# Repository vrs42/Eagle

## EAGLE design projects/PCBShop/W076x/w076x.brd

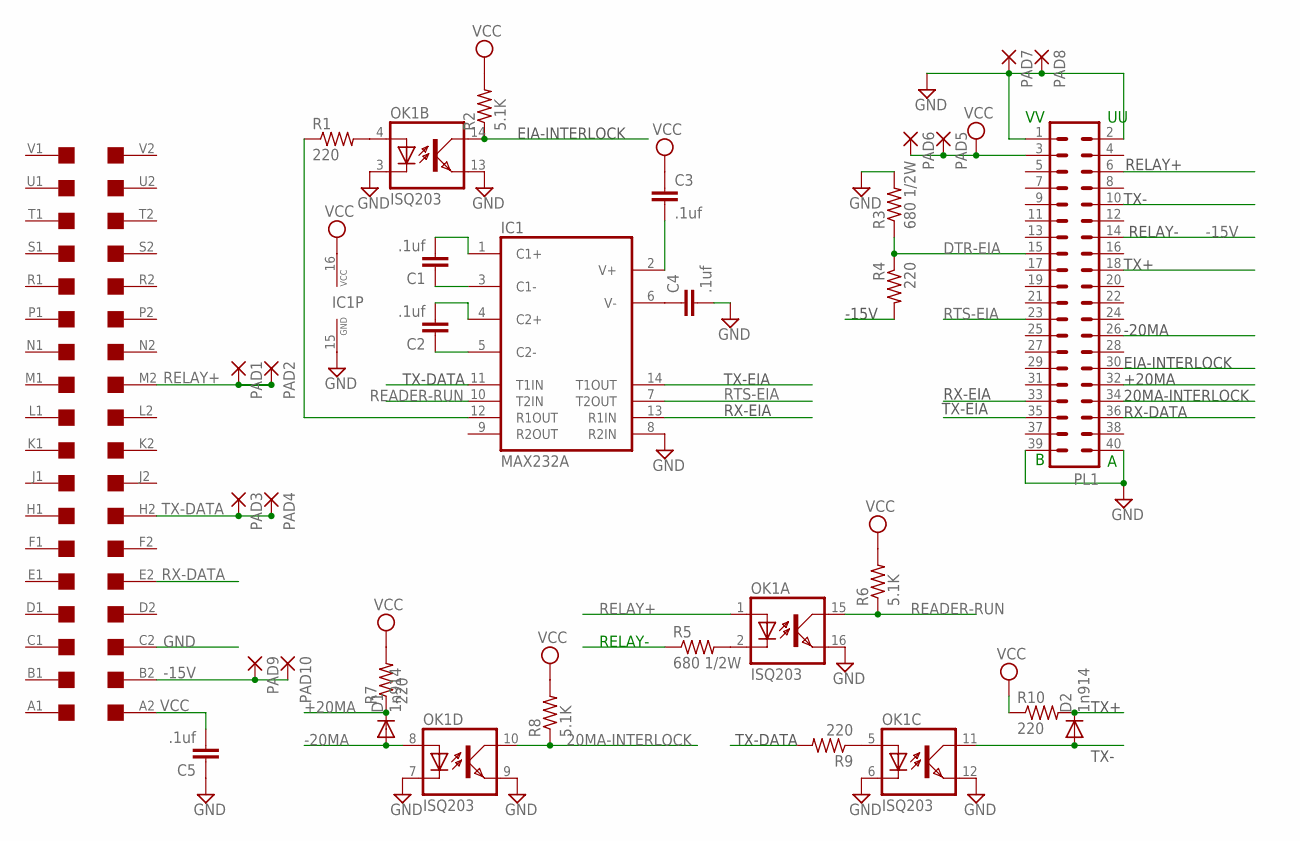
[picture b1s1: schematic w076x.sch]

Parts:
C1, C2, C3, C4, C5: .1uf; C050-025X075
D1, D2: 1n914; DO41-10
IC1: MAX232A; DIL16
OK1: ISQ203; DIL16
PAD1, PAD2, PAD3, PAD4, PAD5, PAD6, PAD7, PAD8, PAD9, PAD10: 1,6/0,8
PL1: 40H
R1, R4, R7, R9, R10: 220; 0207/10
R2, R6, R8: 5.1K; 0207/10
R3, R5: 680 1/2W; 0207/12
U$1: DEC-FLIPCHIP

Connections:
20MA-INTERLOCK: OK1.10 (COL), PL1.34, R8.1
+20MA: D1.C, PL1.32, R7.1
-15V: PAD9.1, PAD10.1, PL1.14, R4.2, R5.1, U$1.B2
-20MA: D1.A, OK1.8 (A), PL1.26
DTR-EIA: PL1.15, R3.1, R4.1
EIA-INTERLOCK: OK1.14 (COL), PL1.30, R2.1
GND: C4.2, C5.1, IC1.8 (R2IN), IC1.15 (GND), OK1.3 (C), OK1.6 (C), OK1.7 (C), OK1.9 (EMIT), OK1.12 (EMIT), OK1.13 (EMIT), OK1.16 (EMIT), PAD7.1, PAD8.1, PL1.1, PL1.2, PL1.39, PL1.40, R3.2, U$1.C2
unnamed: C2.1, IC1.5 (C2-)
unnamed: C2.2, IC1.4 (C2+)
unnamed: C1.2, IC1.1 (C1+)
unnamed: C1.1, IC1.3 (C1-)
unnamed: OK1.2 (C), R5.2
unnamed: IC1.12 (R1OUT), R1.1
unnamed: C3.2, IC1.2 (V+)
unnamed: C4.1, IC1.6 (V-)
unnamed: OK1.4 (A), R1.2
unnamed: OK1.5 (A), R9.1
READER-RUN: IC1.10 (T2IN), OK1.15 (COL), R6.1
RELAY+: OK1.1 (A), PAD1.1, PAD2.1, PL1.6, U$1.M2
RTS-EIA: IC1.7 (T2OUT), PL1.23
RX-DATA: PL1.36, U$1.E2
RX-EIA: IC1.13 (R1IN), PL1.33
TX+: D2.C, PL1.18, R10.2
TX-: D2.A, OK1.11 (COL), PL1.10
TX-DATA: IC1.11 (T1IN), PAD3.1, PAD4.1, R9.2, U$1.H2
TX-EIA: IC1.14 (T1OUT), PL1.35
VCC: C3.1, C5.2, IC1.16 (VCC), PAD5.1, PAD6.1, PL1.3, R2.2, R6.2, R7.2, R8.2, R10.1, U$1.A2

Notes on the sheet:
TX-
TX+
RX-EIA
TX-EIA
-20MA
EIA-INTERLOCK
+20MA
20MA-INTERLOCK
RX-DATA
RELAY+
RELAY-
TX-DATA
-15V

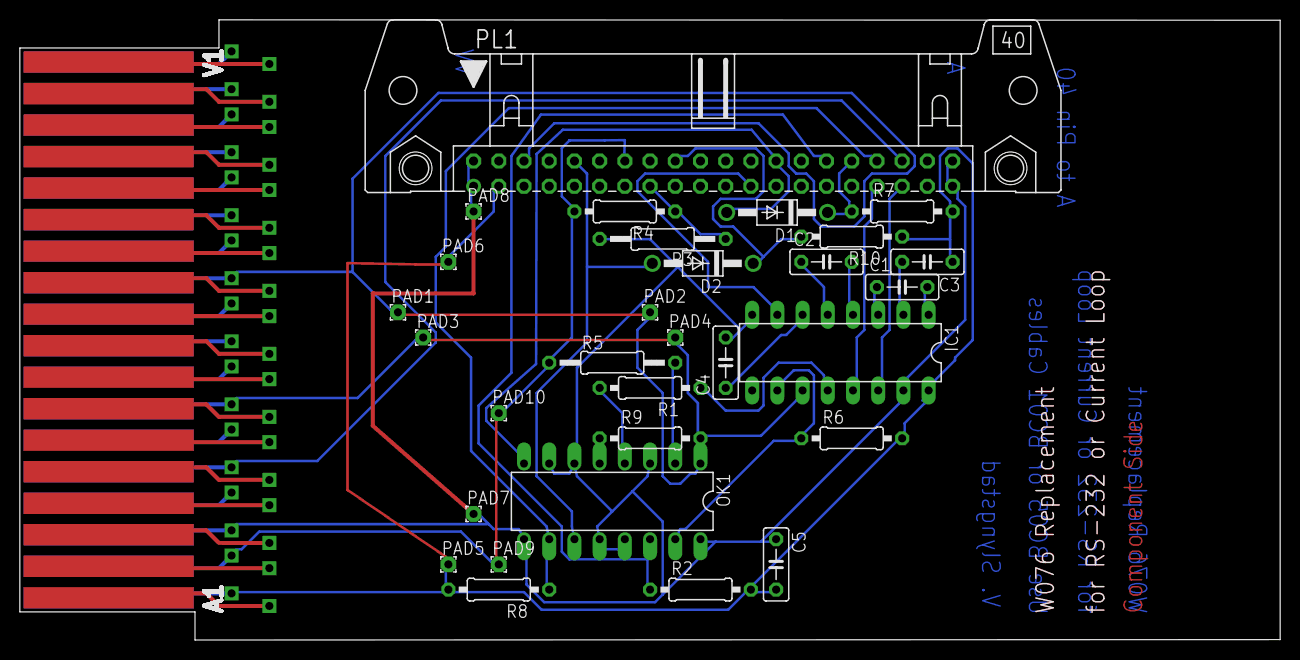
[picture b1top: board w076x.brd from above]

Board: 2 copper layers, 127.0 x 62.5 mm, 31 parts (0 on the bottom side), 27 nets.

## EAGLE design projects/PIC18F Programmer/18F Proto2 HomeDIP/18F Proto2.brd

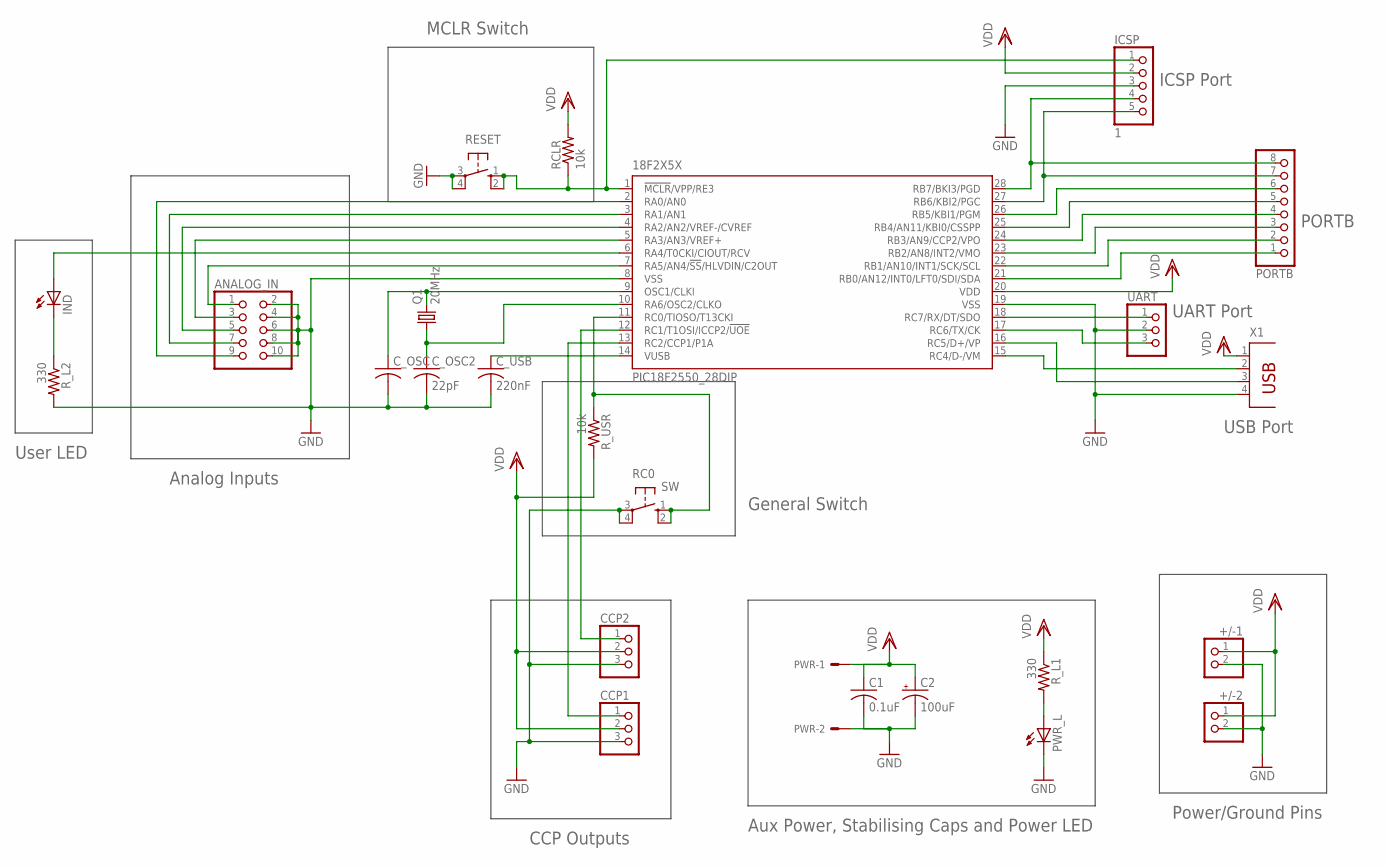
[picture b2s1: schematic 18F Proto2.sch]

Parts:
18F2X5X: PIC18F2550_28DIP; DIL28-3
+/-1, +/-2: PINHD-1X2; 1X02
ANALOG_IN: PINHD-2X5; 2X05
C1: 0.1uF; C050-025X075
C2: 100uF; E2,5-6
CCP1, CCP2: PINHD-1X3; 1X03
C_OSC: C-US025-025X050; C025-025X050
C_OSC2: 22pF; C025-025X050
C_USB: 220nF; C050-025X075
ICSP: 1; 1X05
IND: LED3MM
PORTB: PINHD-1X8; 1X08
PWR: 22-23-2021
PWR_L: LED3MM
Q1: 20MHz; HC49/S
RC0: SW; B3F-10XX
RCLR: 10k; 0204/7
RESET: 10-XX; B3F-10XX
R_L1: 330; 0204/7
R_L2: 330; 0207/10
R_USR: 10k; 0204/7
UART: PINHD-1X3; 1X03
X1: PN61729

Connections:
D+: 18F2X5X.16 (RC5/D+/VP), X1.3
D-: 18F2X5X.15 (RC4/D-/VM), X1.2
GND: 18F2X5X.8 (VSS), 18F2X5X.19 (VSS), +/-1.2, +/-2.2, ANALOG_IN.2, ANALOG_IN.4, ANALOG_IN.6, ANALOG_IN.8, ANALOG_IN.10, C1.2, C2.-, CCP1.3, CCP2.3, C_OSC.2, C_OSC2.2, C_USB.2, ICSP.3, PWR.2, PWR_L.K (C), RC0.3, RC0.4 (P1), RESET.3, RESET.4 (P1), R_L2.2, UART.2, X1.4
MCLR: 18F2X5X.1 (!MCLR!/VPP/RE3), ICSP.1, RCLR.1, RESET.1 (S), RESET.2 (S1)
unnamed: 18F2X5X.10 (RA6/OSC2/CLKO), C_OSC2.1, Q1.1
unnamed: PWR_L.A, R_L1.2
unnamed: 18F2X5X.9 (OSC1/CLKI), C_OSC.1, Q1.2
unnamed: 18F2X5X.14 (VUSB), C_USB.1
unnamed: 18F2X5X.2 (RA0/AN0), ANALOG_IN.9
unnamed: 18F2X5X.3 (RA1/AN1), ANALOG_IN.7
unnamed: 18F2X5X.4 (RA2/AN2/VREF-/CVREF), ANALOG_IN.5
unnamed: 18F2X5X.5 (RA3/AN3/VREF+), ANALOG_IN.3
unnamed: 18F2X5X.6 (RA4/T0CKI/CIOUT/RCV), IND.A
unnamed: 18F2X5X.7 (RA5/AN4/!SS!/HLVDIN/C2OUT), ANALOG_IN.1
unnamed: IND.K (C), R_L2.1
unnamed: 18F2X5X.11 (RC0/TIOSO/T13CKI), RC0.1 (S), RC0.2 (S1), R_USR.1
unnamed: 18F2X5X.12 (RC1/T1OSI/ICCP2/!UOE), CCP2.1
unnamed: 18F2X5X.13 (RC2/CCP1/P1A), CCP1.1
unnamed: 18F2X5X.21 (RB0/AN12/INT0/LFT0/SDI/SDA), PORTB.1
unnamed: 18F2X5X.22 (RB1/AN10/INT1/SCK/SCL), PORTB.2
unnamed: 18F2X5X.23 (RB2/AN8/INT2/VMO), PORTB.3
unnamed: 18F2X5X.24 (RB3/AN9/CCP2/VPO), PORTB.4
unnamed: 18F2X5X.25 (RB4/AN11/KBI0/CSSPP), PORTB.5
unnamed: 18F2X5X.26 (RB5/KBI1/PGM), PORTB.6
PGC: 18F2X5X.27 (RB6/KBI2/PGC), ICSP.5, PORTB.7
PGD: 18F2X5X.28 (RB7/BKI3/PGD), ICSP.4, PORTB.8
RX: 18F2X5X.18 (RC7/RX/DT/SDO), UART.1
TX: 18F2X5X.17 (RC6/TX/CK), UART.3
VDD: 18F2X5X.20 (VDD), +/-1.1, +/-2.1, C1.1, C2.+, CCP1.2, CCP2.2, ICSP.2, PWR.1, RCLR.2, R_L1.1, R_USR.2, X1.1

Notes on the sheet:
Power/Ground Pins
Aux Power, Stabilising Caps and Power LED
General Switch
User LED
Analog Inputs
CCP Outputs
MCLR Switch
ICSP Port
PORTB
UART Port
USB Port

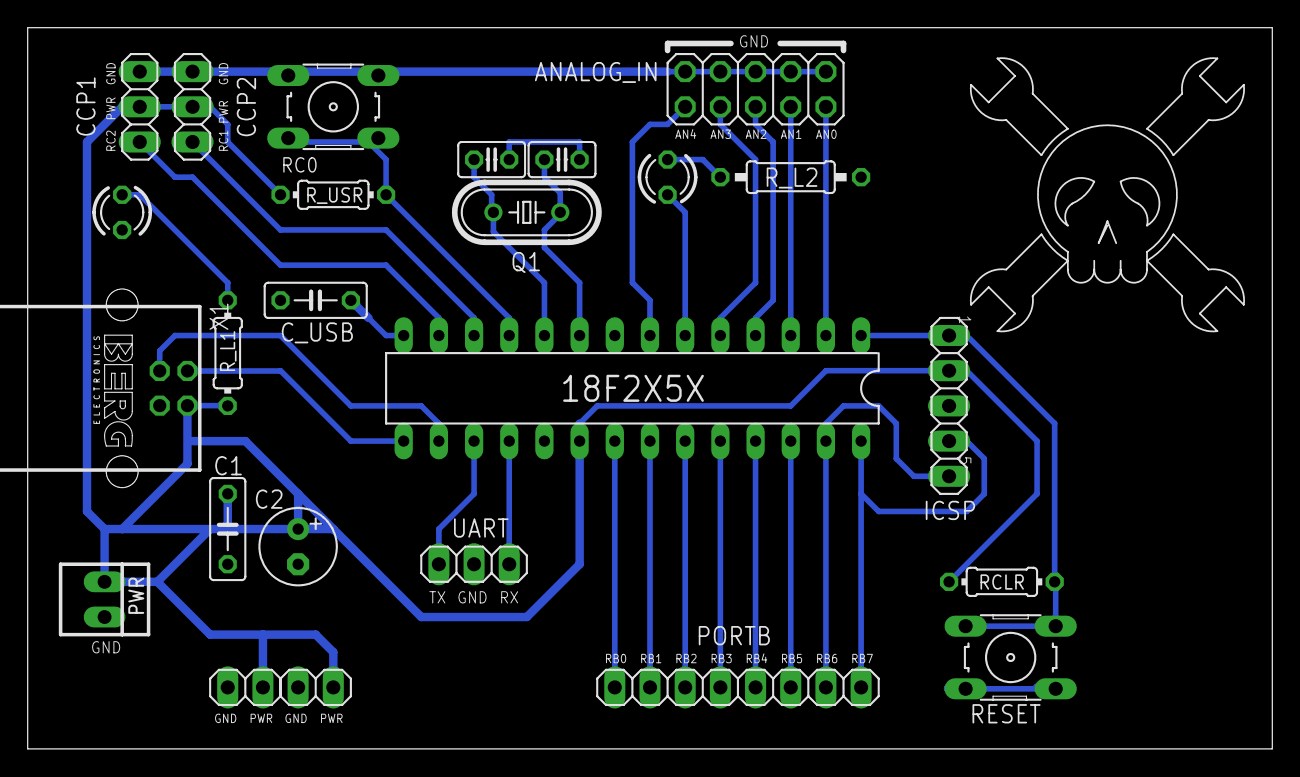
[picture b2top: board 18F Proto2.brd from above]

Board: 2 copper layers, 89.8 x 52.1 mm, 26 parts (0 on the bottom side), 29 nets.

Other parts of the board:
U$1: HACKADAY_S

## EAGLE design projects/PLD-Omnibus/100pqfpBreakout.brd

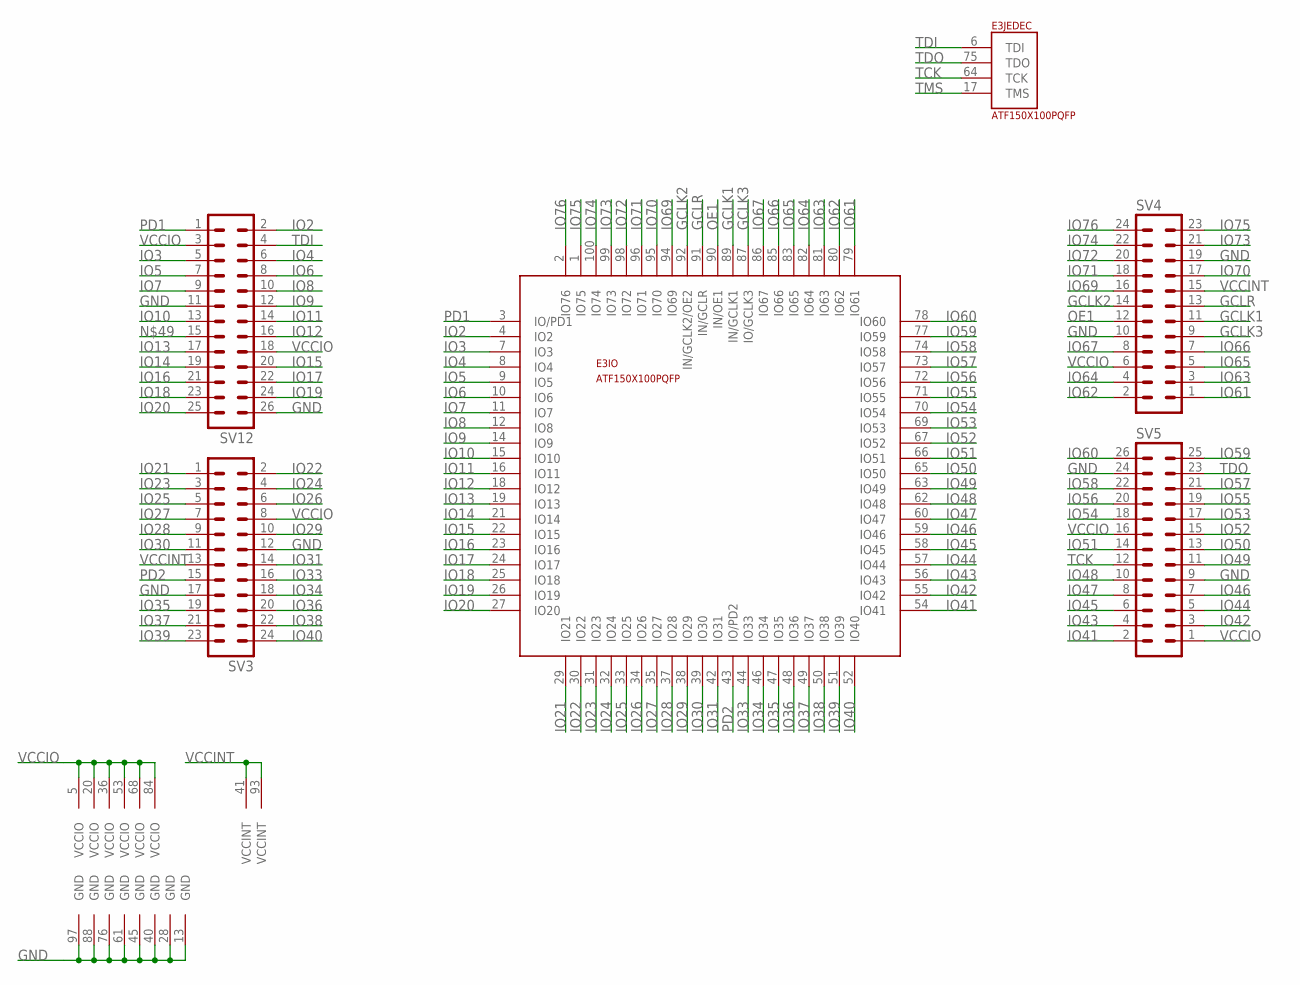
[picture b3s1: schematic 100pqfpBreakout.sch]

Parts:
E3: ATF150X100PQFP; PQFP-100
SV3, SV4: MA12-2
SV5, SV12: MA13-2

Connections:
GCLK1: E3.89 (IN/GCLK1), SV4.11
GCLK2: E3.92 (IN/GCLK2/OE2), SV4.14
GCLK3: E3.87 (IO/GCLK3), SV4.9
GCLR: E3.91 (IN/GCLR), SV4.13
GND: E3.13 (GND), E3.28 (GND), E3.40 (GND), E3.45 (GND), E3.61 (GND), E3.76 (GND), E3.88 (GND), E3.97 (GND), SV3.12, SV3.17, SV4.10, SV4.19, SV5.9, SV5.24, SV12.11, SV12.26
IO2: E3.4 (IO2), SV12.2
IO3: E3.7 (IO3), SV12.5
IO4: E3.8 (IO4), SV12.6
IO5: E3.9 (IO5), SV12.7
IO6: E3.10 (IO6), SV12.8
IO7: E3.11 (IO7), SV12.9
IO8: E3.12 (IO8), SV12.10
IO9: E3.14 (IO9), SV12.12
IO10: E3.15 (IO10), SV12.13
IO11: E3.16 (IO11), SV12.14
IO12: E3.18 (IO12), SV12.16
IO13: E3.19 (IO13), SV12.17
IO14: E3.21 (IO14), SV12.19
IO15: E3.22 (IO15), SV12.20
IO16: E3.23 (IO16), SV12.21
IO17: E3.24 (IO17), SV12.22
IO18: E3.25 (IO18), SV12.23
IO19: E3.26 (IO19), SV12.24
IO20: E3.27 (IO20), SV12.25
IO21: E3.29 (IO21), SV3.1
IO22: E3.30 (IO22), SV3.2
IO23: E3.31 (IO23), SV3.3
IO24: E3.32 (IO24), SV3.4
IO25: E3.33 (IO25), SV3.5
IO26: E3.34 (IO26), SV3.6
IO27: E3.35 (IO27), SV3.7
IO28: E3.37 (IO28), SV3.9
IO29: E3.38 (IO29), SV3.10
IO30: E3.39 (IO30), SV3.11
IO31: E3.42 (IO31), SV3.14
IO33: E3.44 (IO33), SV3.16
IO34: E3.46 (IO34), SV3.18
IO35: E3.47 (IO35), SV3.19
IO36: E3.48 (IO36), SV3.20
IO37: E3.49 (IO37), SV3.21
IO38: E3.50 (IO38), SV3.22
IO39: E3.51 (IO39), SV3.23
IO40: E3.52 (IO40), SV3.24
IO41: E3.54 (IO41), SV5.2
IO42: E3.55 (IO42), SV5.3
IO43: E3.56 (IO43), SV5.4
IO44: E3.57 (IO44), SV5.5
IO45: E3.58 (IO45), SV5.6
IO46: E3.59 (IO46), SV5.7
IO47: E3.60 (IO47), SV5.8
IO48: E3.62 (IO48), SV5.10
IO49: E3.63 (IO49), SV5.11
IO50: E3.65 (IO50), SV5.13
IO51: E3.66 (IO51), SV5.14
IO52: E3.67 (IO52), SV5.15
IO53: E3.69 (IO53), SV5.17
IO54: E3.70 (IO54), SV5.18
IO55: E3.71 (IO55), SV5.19
IO56: E3.72 (IO56), SV5.20
IO57: E3.73 (IO57), SV5.21
IO58: E3.74 (IO58), SV5.22
IO59: E3.77 (IO59), SV5.25
IO60: E3.78 (IO60), SV5.26
IO61: E3.79 (IO61), SV4.1
IO62: E3.80 (IO62), SV4.2
IO63: E3.81 (IO63), SV4.3
IO64: E3.82 (IO64), SV4.4
IO65: E3.83 (IO65), SV4.5
IO66: E3.85 (IO66), SV4.7
IO67: E3.86 (IO67), SV4.8
IO69: E3.94 (IO69), SV4.16
IO70: E3.95 (IO70), SV4.17
IO71: E3.96 (IO71), SV4.18
IO72: E3.98 (IO72), SV4.20
IO73: E3.99 (IO73), SV4.21
IO74: E3.100 (IO74), SV4.22
IO75: E3.1 (IO75), SV4.23
IO76: E3.2 (IO76), SV4.24
OE1: E3.90 (IN/OE1), SV4.12
PD1: E3.3 (IO/PD1), SV12.1
PD2: E3.43 (IO/PD2), SV3.15
TCK: E3.64 (TCK), SV5.12
TDI: E3.6 (TDI), SV12.4
TDO: E3.75 (TDO), SV5.23
TMS: E3.17 (TMS)
VCCINT: E3.41 (VCCINT), E3.93 (VCCINT), SV3.13, SV4.15
VCCIO: E3.5 (VCCIO), E3.20 (VCCIO), E3.36 (VCCIO), E3.53 (VCCIO), E3.68 (VCCIO), E3.84 (VCCIO), SV3.8, SV4.6, SV5.1, SV5.16, SV12.3, SV12.18

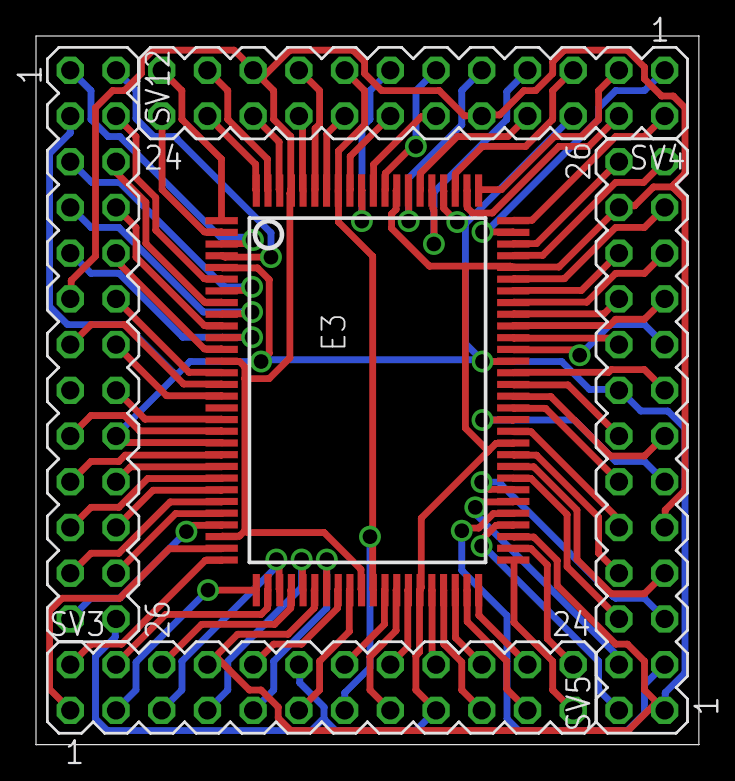
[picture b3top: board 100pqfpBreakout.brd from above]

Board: 2 copper layers, 36.8 x 39.4 mm, 5 parts (0 on the bottom side), 86 nets.

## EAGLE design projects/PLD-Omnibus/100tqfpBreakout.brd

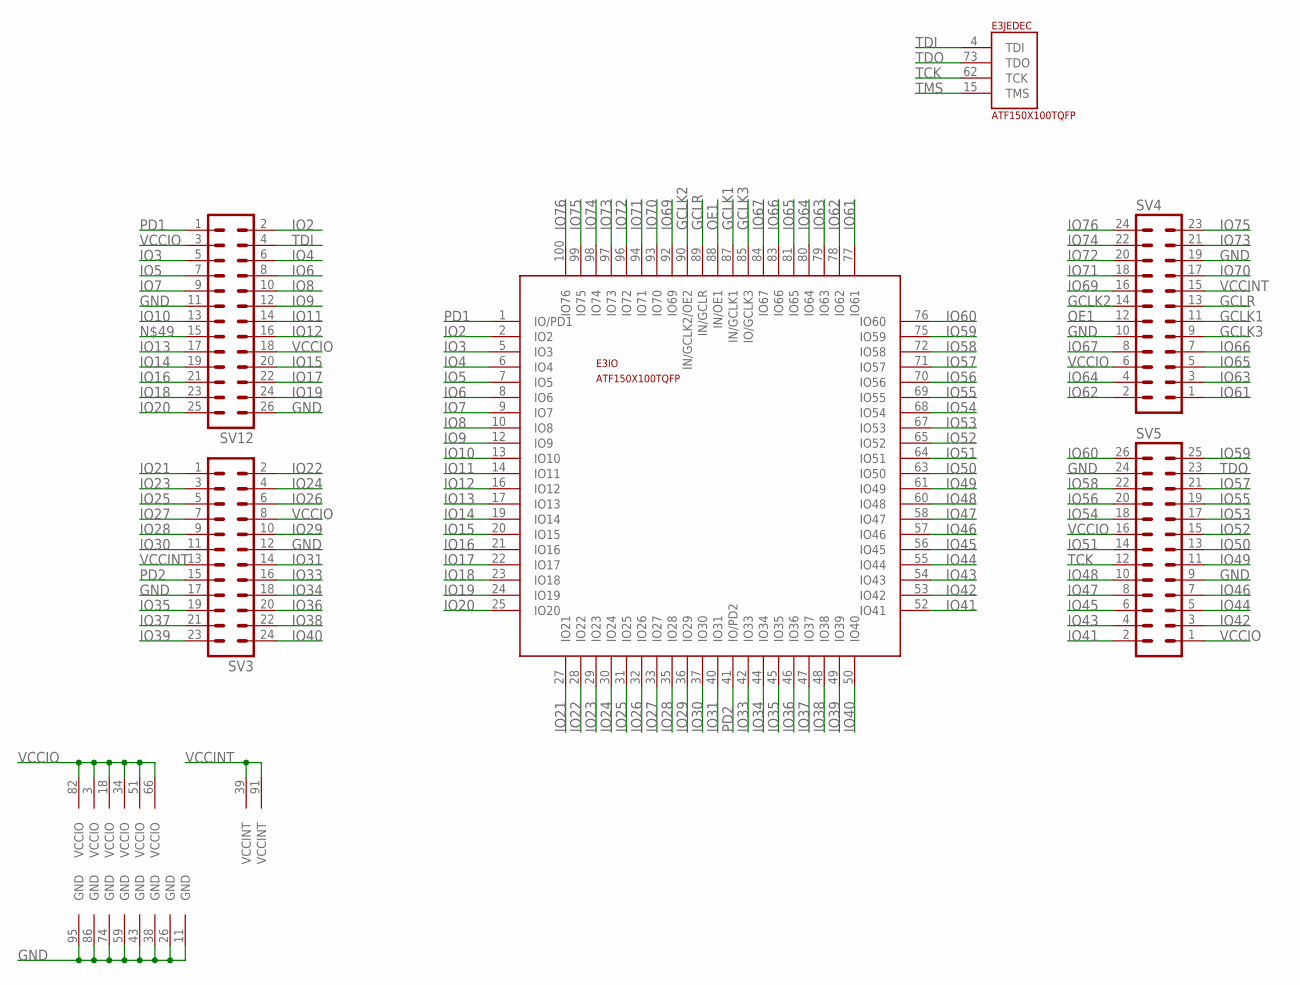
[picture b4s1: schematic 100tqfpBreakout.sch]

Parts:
E3: ATF150X100TQFP; TQFP-100
SV3, SV4: MA12-2
SV5, SV12: MA13-2

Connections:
GCLK1: E3.87 (IN/GCLK1), SV4.11
GCLK2: E3.90 (IN/GCLK2/OE2), SV4.14
GCLK3: E3.85 (IO/GCLK3), SV4.9
GCLR: E3.89 (IN/GCLR), SV4.13
GND: E3.11 (GND), E3.26 (GND), E3.38 (GND), E3.43 (GND), E3.59 (GND), E3.74 (GND), E3.86 (GND), E3.95 (GND), SV3.12, SV3.17, SV4.10, SV4.19, SV5.9, SV5.24, SV12.11, SV12.26
IO2: E3.2 (IO2), SV12.2
IO3: E3.5 (IO3), SV12.5
IO4: E3.6 (IO4), SV12.6
IO5: E3.7 (IO5), SV12.7
IO6: E3.8 (IO6), SV12.8
IO7: E3.9 (IO7), SV12.9
IO8: E3.10 (IO8), SV12.10
IO9: E3.12 (IO9), SV12.12
IO10: E3.13 (IO10), SV12.13
IO11: E3.14 (IO11), SV12.14
IO12: E3.16 (IO12), SV12.16
IO13: E3.17 (IO13), SV12.17
IO14: E3.19 (IO14), SV12.19
IO15: E3.20 (IO15), SV12.20
IO16: E3.21 (IO16), SV12.21
IO17: E3.22 (IO17), SV12.22
IO18: E3.23 (IO18), SV12.23
IO19: E3.24 (IO19), SV12.24
IO20: E3.25 (IO20), SV12.25
IO21: E3.27 (IO21), SV3.1
IO22: E3.28 (IO22), SV3.2
IO23: E3.29 (IO23), SV3.3
IO24: E3.30 (IO24), SV3.4
IO25: E3.31 (IO25), SV3.5
IO26: E3.32 (IO26), SV3.6
IO27: E3.33 (IO27), SV3.7
IO28: E3.35 (IO28), SV3.9
IO29: E3.36 (IO29), SV3.10
IO30: E3.37 (IO30), SV3.11
IO31: E3.40 (IO31), SV3.14
IO33: E3.42 (IO33), SV3.16
IO34: E3.44 (IO34), SV3.18
IO35: E3.45 (IO35), SV3.19
IO36: E3.46 (IO36), SV3.20
IO37: E3.47 (IO37), SV3.21
IO38: E3.48 (IO38), SV3.22
IO39: E3.49 (IO39), SV3.23
IO40: E3.50 (IO40), SV3.24
IO41: E3.52 (IO41), SV5.2
IO42: E3.53 (IO42), SV5.3
IO43: E3.54 (IO43), SV5.4
IO44: E3.55 (IO44), SV5.5
IO45: E3.56 (IO45), SV5.6
IO46: E3.57 (IO46), SV5.7
IO47: E3.58 (IO47), SV5.8
IO48: E3.60 (IO48), SV5.10
IO49: E3.61 (IO49), SV5.11
IO50: E3.63 (IO50), SV5.13
IO51: E3.64 (IO51), SV5.14
IO52: E3.65 (IO52), SV5.15
IO53: E3.67 (IO53), SV5.17
IO54: E3.68 (IO54), SV5.18
IO55: E3.69 (IO55), SV5.19
IO56: E3.70 (IO56), SV5.20
IO57: E3.71 (IO57), SV5.21
IO58: E3.72 (IO58), SV5.22
IO59: E3.75 (IO59), SV5.25
IO60: E3.76 (IO60), SV5.26
IO61: E3.77 (IO61), SV4.1
IO62: E3.78 (IO62), SV4.2
IO63: E3.79 (IO63), SV4.3
IO64: E3.80 (IO64), SV4.4
IO65: E3.81 (IO65), SV4.5
IO66: E3.83 (IO66), SV4.7
IO67: E3.84 (IO67), SV4.8
IO69: E3.92 (IO69), SV4.16
IO70: E3.93 (IO70), SV4.17
IO71: E3.94 (IO71), SV4.18
IO72: E3.96 (IO72), SV4.20
IO73: E3.97 (IO73), SV4.21
IO74: E3.98 (IO74), SV4.22
IO75: E3.99 (IO75), SV4.23
IO76: E3.100 (IO76), SV4.24
OE1: E3.88 (IN/OE1), SV4.12
PD1: E3.1 (IO/PD1), SV12.1
PD2: E3.41 (IO/PD2), SV3.15
TCK: E3.62 (TCK), SV5.12
TDI: E3.4 (TDI), SV12.4
TDO: E3.73 (TDO), SV5.23
TMS: E3.15 (TMS)
VCCINT: E3.39 (VCCINT), E3.91 (VCCINT), SV3.13, SV4.15
VCCIO: E3.3 (VCCIO), E3.18 (VCCIO), E3.34 (VCCIO), E3.51 (VCCIO), E3.66 (VCCIO), E3.82 (VCCIO), SV3.8, SV4.6, SV5.1, SV5.16, SV12.3, SV12.18

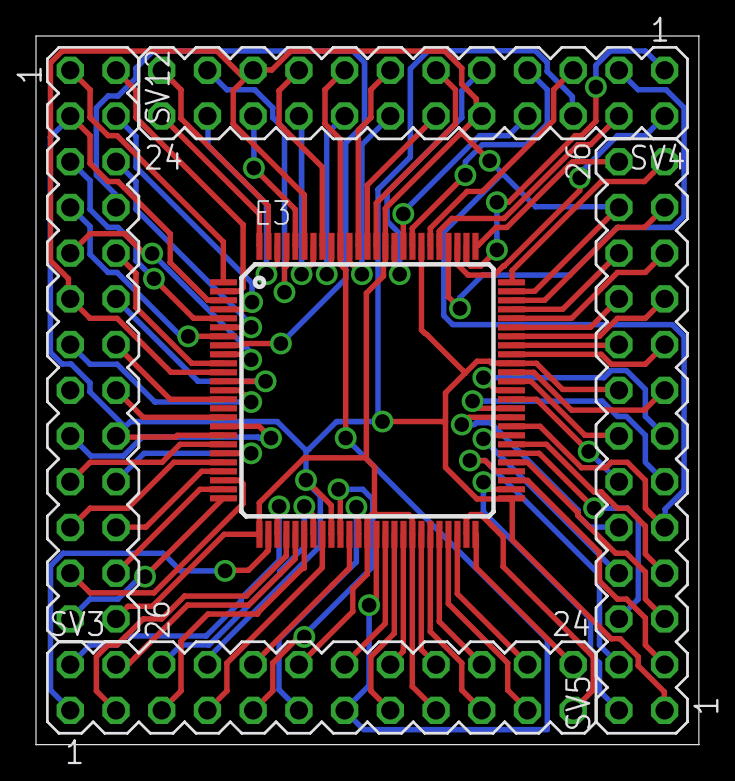
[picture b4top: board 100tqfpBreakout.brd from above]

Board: 2 copper layers, 36.8 x 39.4 mm, 5 parts (0 on the bottom side), 86 nets.

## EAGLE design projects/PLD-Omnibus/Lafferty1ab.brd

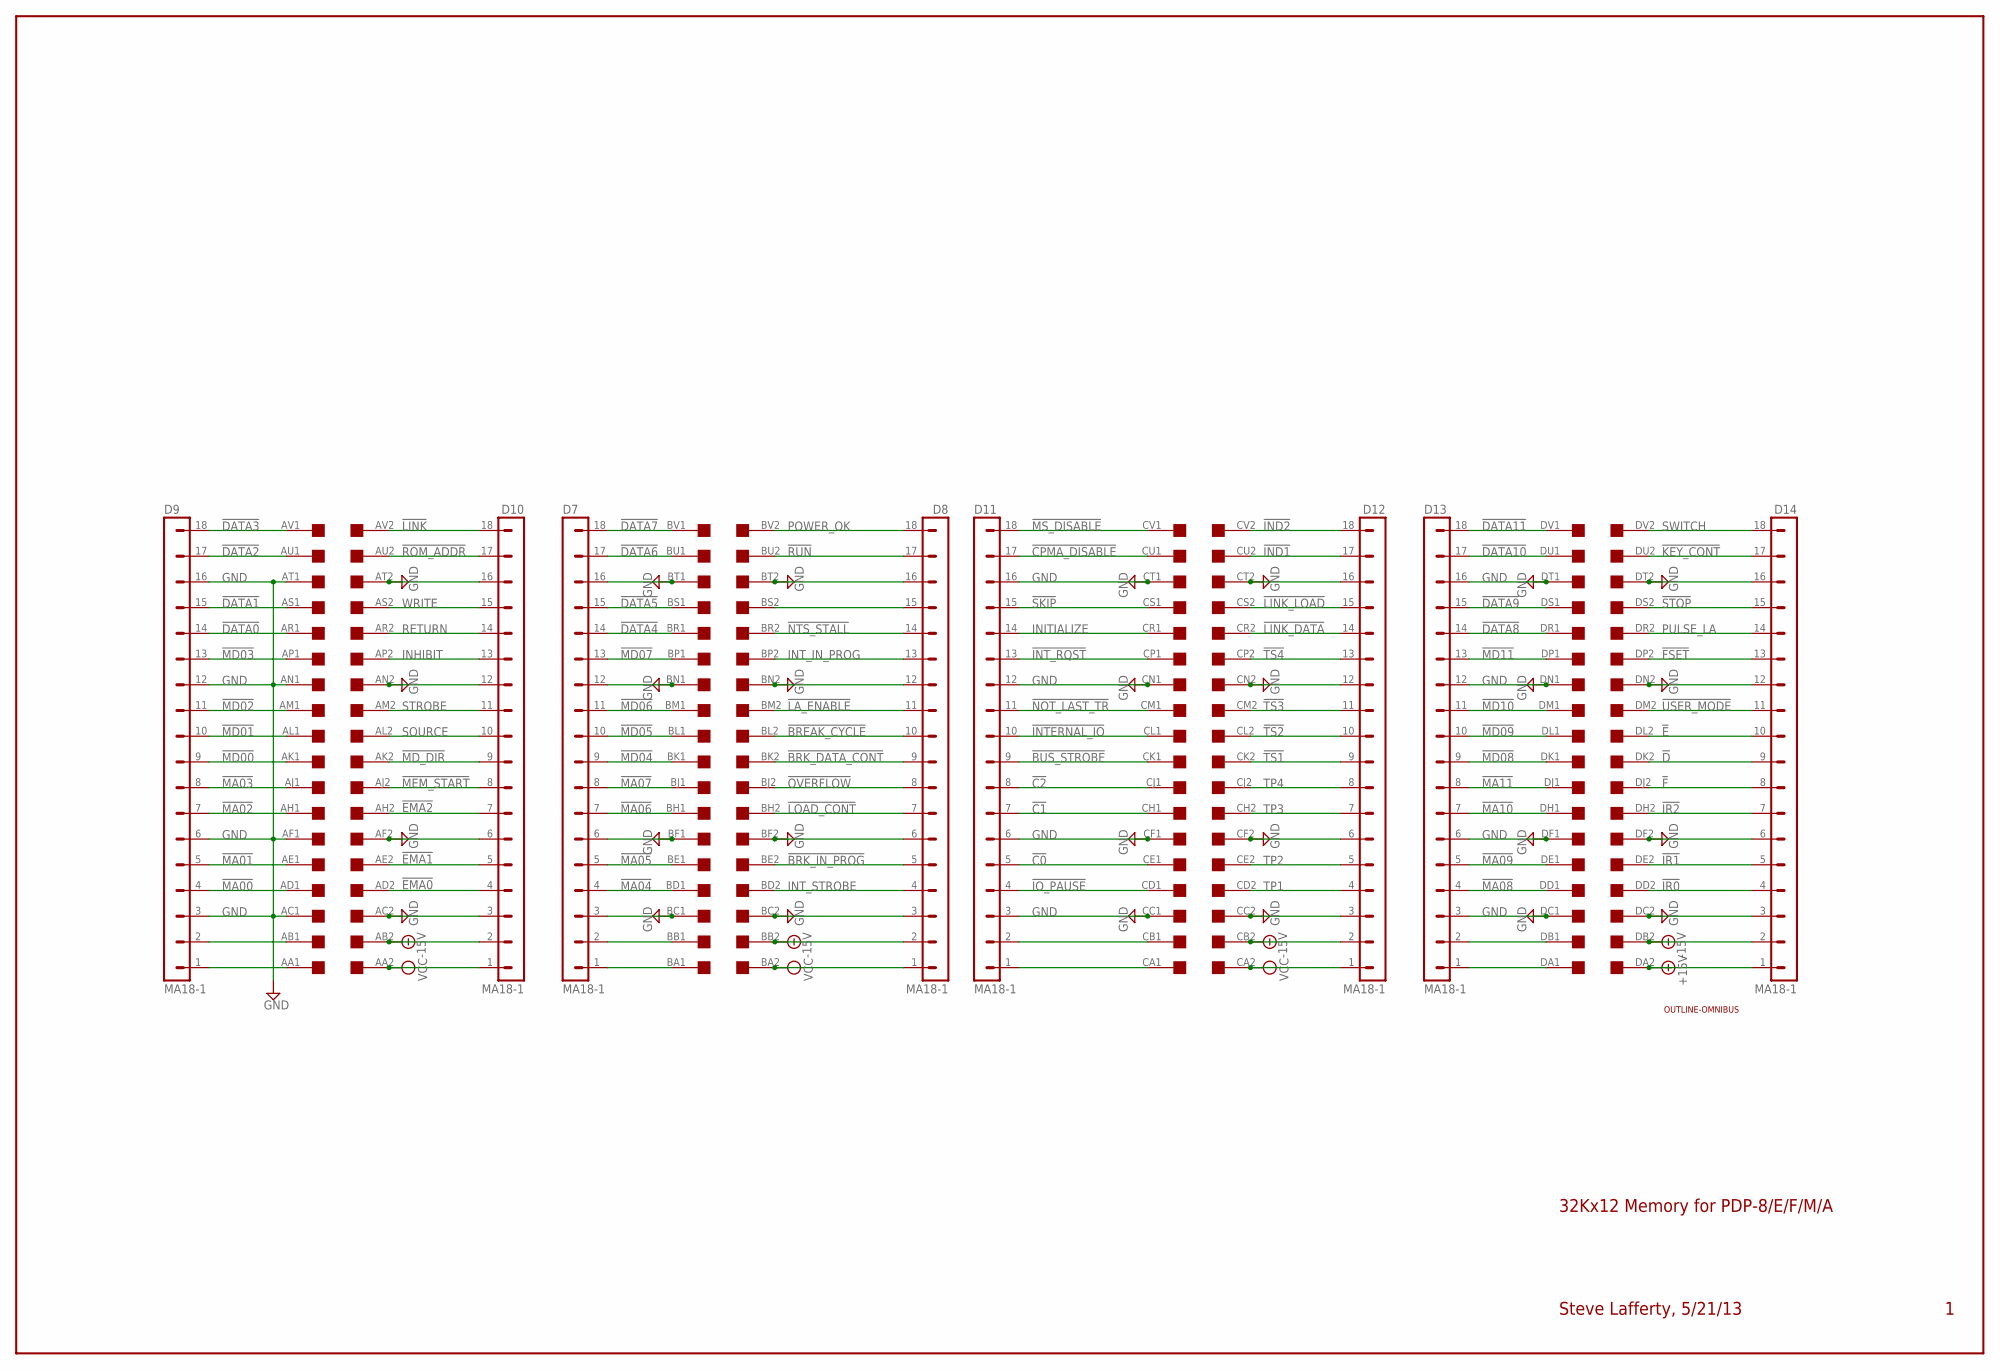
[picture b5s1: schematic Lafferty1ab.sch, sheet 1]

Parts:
D7, D8, D9, D10, D11, D12, D13, D14: MA18-1
U$1: OUTLINE-OMNIBUS; OMNIBUS
U$2: QUAD; EDGE-CON8

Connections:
!BREAK_CYCLE: D8.10, U$2.BL2
!BRK_DATA_CONT: D8.9, U$2.BK2
!BRK_IN_PROG: D8.5, U$2.BE2
!BUS_STROBE: D11.9, U$2.CK1
!C0: D11.5, U$2.CE1
!C1: D11.7, U$2.CH1
!C2: D11.8, U$2.CJ1
!CPMA_DISABLE: D11.17, U$2.CU1
!D: D14.9, U$2.DK2
!DATA0: D9.14, U$2.AR1
!DATA1: D9.15, U$2.AS1
!DATA2: D9.17, U$2.AU1
!DATA3: D9.18, U$2.AV1
!DATA4: D7.14, U$2.BR1
!DATA5: D7.15, U$2.BS1
!DATA6: D7.17, U$2.BU1
!DATA7: D7.18, U$2.BV1
!DATA8: D13.14, U$2.DR1
!DATA9: D13.15, U$2.DS1
!DATA10: D13.17, U$2.DU1
!DATA11: D13.18, U$2.DV1
!E: D14.10, U$2.DL2
!EMA0: D10.4, U$2.AD2; also elsewhere on the board
!EMA1: D10.5, U$2.AE2; also elsewhere on the board
!EMA2: D10.7, U$2.AH2; also elsewhere on the board
!F: D14.8, U$2.DJ2
!FSET: D14.13, U$2.DP2
!IND1: D12.17, U$2.CU2
!IND2: D12.18, U$2.CV2
!INTERNAL_IO: D11.10, U$2.CL1
!INT_RQST: D11.13, U$2.CP1
!IO_PAUSE: D11.4, U$2.CD1
!IR0: D14.4, U$2.DD2
!IR1: D14.5, U$2.DE2
!IR2: D14.7, U$2.DH2
!KEY_CONT: D14.17, U$2.DU2
!LA_ENABLE: D8.11, U$2.BM2
!LINK: D10.18, U$2.AV2
!LINK_DATA: D12.14, U$2.CR2
!LINK_LOAD: D12.15, U$2.CS2
!LOAD_CONT: D8.7, U$2.BH2
!MA00: D9.4, U$2.AD1; also elsewhere on the board
!MA01: D9.5, U$2.AE1; also elsewhere on the board
!MA02: D9.7, U$2.AH1; also elsewhere on the board
!MA03: D9.8, U$2.AJ1; also elsewhere on the board
!MA04: D7.4, U$2.BD1; also elsewhere on the board
!MA05: D7.5, U$2.BE1; also elsewhere on the board
!MA06: D7.7, U$2.BH1; also elsewhere on the board
!MA07: D7.8, U$2.BJ1; also elsewhere on the board
!MA08: D13.4, U$2.DD1; also elsewhere on the board
!MA09: D13.5, U$2.DE1; also elsewhere on the board
!MA10: D13.7, U$2.DH1; also elsewhere on the board
!MA11: D13.8, U$2.DJ1; also elsewhere on the board
!MD00: D9.9, U$2.AK1; also elsewhere on the board
!MD01: D9.10, U$2.AL1; also elsewhere on the board
!MD02: D9.11, U$2.AM1; also elsewhere on the board
!MD03: D9.13, U$2.AP1; also elsewhere on the board
!MD04: D7.9, U$2.BK1; also elsewhere on the board
!MD05: D7.10, U$2.BL1; also elsewhere on the board
!MD06: D7.11, U$2.BM1; also elsewhere on the board
!MD07: D7.13, U$2.BP1; also elsewhere on the board
!MD08: D13.9, U$2.DK1; also elsewhere on the board
!MD09: D13.10, U$2.DL1; also elsewhere on the board
!MD10: D13.11, U$2.DM1; also elsewhere on the board
!MD11: D13.13, U$2.DP1; also elsewhere on the board
!MD_DIR: D10.9, U$2.AK2; also elsewhere on the board
!MEM_START: D10.8, U$2.AJ2
!MS_DISABLE: D11.18, U$2.CV1
!NOT_LAST_TR: D11.11, U$2.CM1
!NTS_STALL: D8.14, U$2.BR2
!OVERFLOW: D8.8, U$2.BJ2
!ROM_ADDR: D10.17, U$2.AU2; also elsewhere on the board
!RUN: D8.17, U$2.BU2
!SKIP: D11.15, U$2.CS1
!STOP: D14.15, U$2.DS2
!TS1: D12.9, U$2.CK2
!TS2: D12.10, U$2.CL2
!TS3: D12.11, U$2.CM2
!TS4: D12.13, U$2.CP2
!USER_MODE: D14.11, U$2.DM2
+15V: D14.1, U$2.DA2
-15V: D8.2, D10.2, D12.2, D14.2, U$2.AB2, U$2.BB2, U$2.CB2, U$2.DB2
GND: D7.3, D7.6, D7.12, D7.16, D8.3, D8.6, D8.12, D8.16, D9.3, D9.6, D9.12, D9.16, D10.3, D10.6, D10.12, D10.16, D11.3, D11.6, D11.12, D11.16, D12.3, D12.6, D12.12, D12.16, D13.3, D13.6, D13.12, D13.16, D14.3, D14.6, D14.12, D14.16, U$2.AC1, U$2.AC2, U$2.AF1, U$2.AF2, U$2.AN1, U$2.AN2, U$2.AT1, U$2.AT2, U$2.BC1, U$2.BC2, U$2.BF1, U$2.BF2, U$2.BN1, U$2.BN2, U$2.BT1, U$2.BT2, U$2.CC1, U$2.CC2, U$2.CF1, U$2.CF2, U$2.CN1, U$2.CN2, U$2.CT1, U$2.CT2, U$2.DC1, U$2.DC2, U$2.DF1, U$2.DF2, U$2.DN1, U$2.DN2, U$2.DT1, U$2.DT2; also elsewhere on the board
INHIBIT: D10.13, U$2.AP2
INITIALIZE: D11.14, U$2.CR1
INT_IN_PROG: D8.13, U$2.BP2
INT_STROBE: D8.4, U$2.BD2
unnamed: D9.2, U$2.AB1
unnamed: D9.1, U$2.AA1
unnamed: D7.2, U$2.BB1
unnamed: D7.1, U$2.BA1
unnamed: D11.1, U$2.CA1
unnamed: D8.15, U$2.BS2
unnamed: D11.2, U$2.CB1
unnamed: D13.1, U$2.DA1
unnamed: D13.2, U$2.DB1
POWER_OK: D8.18, U$2.BV2; also elsewhere on the board
PULSE_LA: D14.14, U$2.DR2
RETURN: D10.14, U$2.AR2
SOURCE: D10.10, U$2.AL2; also elsewhere on the board
STROBE: D10.11, U$2.AM2
SWITCH: D14.18, U$2.DV2
TP1: D12.4, U$2.CD2
TP2: D12.5, U$2.CE2
TP3: D12.7, U$2.CH2
TP4: D12.8, U$2.CJ2
VCC: D8.1, D10.1, D12.1, U$2.AA2, U$2.BA2, U$2.CA2; also elsewhere on the board
WRITE: D10.15, U$2.AS2; also elsewhere on the board

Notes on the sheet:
32Kx12 Memory for PDP-8/E/F/M/A
Steve Lafferty, 5/21/13
